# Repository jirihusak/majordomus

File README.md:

# Majordmus - Open source system for Smart Home
 
## About
 
**Majordomus** is a modular automation system built on open standards. It fills the gap between closed, expensive commercial solutions and unreliable consumer-grade components — designed to be repairable, expandable, and to last for decades.
  
## Features
 
- 🧩 **Modular hardware** — base unit + interchangeable modules ( I/O, sensors)
- 🔌 **Standardized interface** — RS-485 / ModBus HW interface, MQTT SW interface
- 🔓 **Vendor lock-in free** — open hardware, open software, your choice
- 🧠 **Node-RED inside** — visual programming for automation flows
- 🧠 **Home Assistant interface** — MQTT integration for popular platform
- 📡 **Offline-first** — works without internet, cloud is optional
## Use Cases
 
| Domain | Examples |
|---|---|
| 🏠 Smart home | lighting, heating, blinds, security, energy management |
| 🏭 Industry | machine control, data acquisition, monitoring, alarms |
| 📊 Monitoring | weather, air quality, energy meters, IoT sensors |
 
## Architecture
 
```
   ┌─────────────────────┐
   │      node-RED       │
   │   Home Assistant    │
   └──────────┬──────────┘
              │
             MQTT
              │
   ┌──────────┴──────────┐
   │ Majordomus Control  │
   │    MQTT bridge      │
   └──────────┬──────────┘
              │
       Modbus / RS-485
              │
    ┌─────────┼─────────┐
    │         │         │
   Unit A   Unit B   Unit C
  (+ modules) (+ modules) (+ modules)
```
 
## Hardware
 
### 🌡️ RoomSensor
 
All-in-one ambient monitoring unit for indoor environments.
 
- 🌡️ Temperature & humidity
- 💨 CO₂, VOC & NOx measurement
- 🚶 PIR motion detection
- ☀️ Ambient light (lux)
- 🔊 Ambient noise measurement
- 🖥️ Display with 3 buttons
- 🔔 Piezo buzzer for acoustic signaling
- 🔌 Digital I/O for door/window contacts or local buttons
- 🔗 I²C port for external sensors
- 🏠 Wall-mount

### 🔲 BoxIO
 
Compact relay & input unit for in-wall or junction-box installation.
 
- ⚡ Replaceable relay outputs (electromagnetic or SSR)
- 🔘 Digital inputs for buttons
- 📊 Hardware input counters for energy monitoring
- 🎛️ Manual control of all outputs (AUTO / MAN ON / MAN OFF)
- 🔗 I²C port for external sensors

### 🎛️ RoomIO
 
Multi-purpose I/O unit for room-level automation and control.
 
- 🔘 Digital inputs & outputs
- 📥 Analog inputs (ADC) — 0–10 V
- 📤 Analog outputs (DAC) — 0–10 V for dimming, fan speed, valves
- 📊 Hardware input counters for energy monitoring
- 🔗 I²C port for external sensors

Schematics and BOMs live in [`hardware/`](hardware/).
 
## Software
 
### **Majordomus Control**
Bridge from HW modules to MQTT interface

### **Node-RED - Custom Node-RED nodes**

## Documentation

- [Documentation web](https://jirihusak.github.io/majordomus/cs/) 

## Contributing
 
Contributions welcome — hardware, firmware, Node-RED flows, or docs.

## Contact
 
- **Web:** [majordomus.tech](https://majordomus.tech)

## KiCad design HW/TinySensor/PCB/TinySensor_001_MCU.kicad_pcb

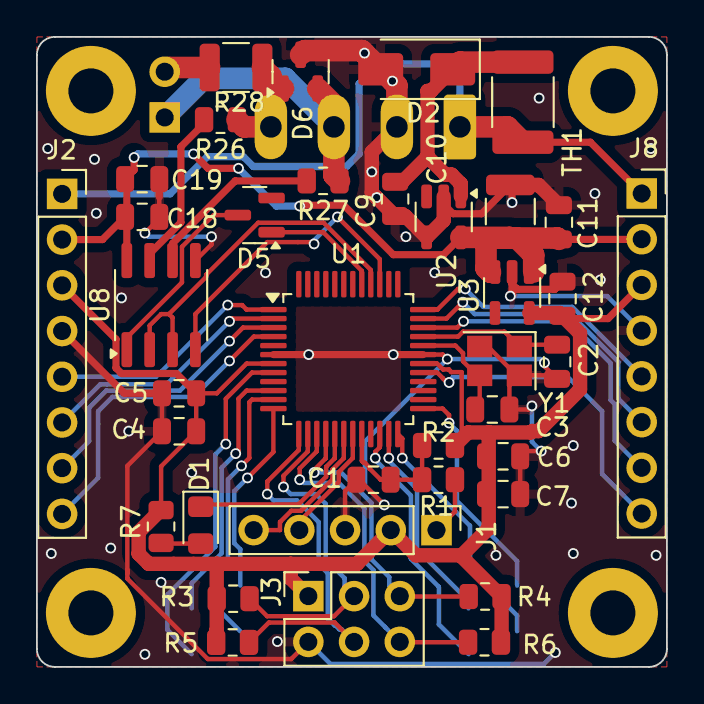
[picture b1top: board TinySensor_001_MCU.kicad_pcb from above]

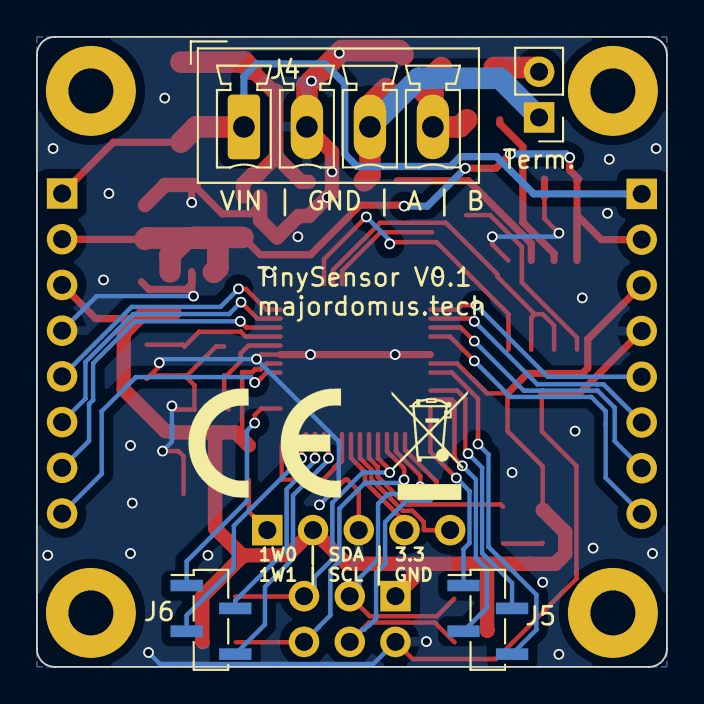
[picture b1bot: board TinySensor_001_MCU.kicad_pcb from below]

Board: 2 copper layers, 35.0 x 35.0 mm, 45 parts (4 on the bottom side), 42 nets.

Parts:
 : MountingHole_2.5mm_Pad
 #2,  #3,  #4: MountingHole_2.5mm_Pad
C1, C5, C6, C11, C18: 100nF; C_0805_2012Metric
C2, C3: 18pF; C_0805_2012Metric
C4, C7, C9, C12, C19: 1uF; C_0805_2012Metric
C10: 2.2uF; C_1210_3225Metric
D1: LED; LED_0805_2012Metric_Pad1.15x1.40mm_HandSolder
D2: SMAJ28; D_SMA
D5: BAS70LT1G; SOT-23
D6: D_TVS_x2_AAC; SOT-23
J1: CONN_DEBUG; PinHeader_1x05_P2.54mm_Vertical
J2, J8: Conn_01x08; PinSocket_1x08_P2.54mm_Vertical
J3: Conn_02x03_Odd_Even; PinSocket_2x03_P2.54mm_Vertical
J4: Conn_01x04; PhoenixContact_MCV_1,5_4-G-3.5_1x04_P3.50mm_Vertical
J5, J6: Conn_01x04; PinSocket_1x04_P1.27mm_Vertical_SMD_Pin1Left
R1: 10k; R_0805_2012Metric
R2: 100R; R_0805_2012Metric
R3, R4, R5, R6: 4k7; R_0805_2012Metric
R7: 1k; R_0805_2012Metric
R26, R27: 10R; R_0805_2012Metric
R28: 120R; R_1210_3225Metric
TH1: MF-MSMF050-2; Fuse_1812_4532Metric_Pad1.30x3.40mm_HandSolder
Term.: Jumper; PinHeader_1x02_P2.54mm_Vertical
U1: PIC18F57K42; TQFP-48_7x7mm_P0.5mm
U2: TPS709; SOT-23-5
U3: TLV70233DBVR; SOT-23-5
U8: SN65HVD3082EDR; SOIC-8_3.9x4.9mm_P1.27mm
Y1: Crystal_GND24; Crystal_SMD_SeikoEpson_FA238-4Pin_3.2x2.5mm

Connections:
+3.3V: C4.1, C5.1, C6.1, C7.1, C12.1, J1.2, J2.3, J3.1, J8.3, R1.1, R3.1, R4.1, R5.2, R6.2, R7.1, U1.7 (VDD), U1.30 (VDD), U3.5 (OUT)
+5V: C10.1, C11.1, C18.1, C19.1, J2.2, J8.2, U2.5 (OUT), U3.1 (IN), U3.3 (EN), U8.8 (VCC)
+12V: J2.1, J4.1, J8.1, TH1.2
/Connectors/RS485-A: D6.2 (A2), J4.3, R27.1, Term..1
/Connectors/RS485-B: D6.1 (A1), J4.4, R26.1, R28.2
/MCU_PIC18/A1: J6.4, U1.22 (RA1)
/MCU_PIC18/A2: J6.2, U1.23 (RA2)
/MCU_PIC18/A3: J6.3, U1.24 (RA3)
/MCU_PIC18/A4: J6.1, U1.25 (RA4)
/MCU_PIC18/B0: J5.4, U1.8 (RB0)
/MCU_PIC18/B2: J5.2, U1.10 (RB2)
/MCU_PIC18/B3: J5.3, U1.11 (RB3)
/MCU_PIC18/B4: J3.5, R4.2, U1.16 (RB4)
/MCU_PIC18/C0: J8.7, U1.34 (RC0)
/MCU_PIC18/C1: J8.6, U1.35 (RC1)
/MCU_PIC18/C7: J2.5, U1.1 (RC7)
/MCU_PIC18/D4: J2.6, U1.2 (RD4)
/MCU_PIC18/D5: J2.7, U1.3 (RD5)
/MCU_PIC18/D6: J2.8, U1.4 (RD6)
/MCU_PIC18/E2: J8.8, U1.29 (RE2)
/MCU_PIC18/F0: J8.5, U1.36 (RF0)
/MCU_PIC18/F4: J5.1, U1.12 (RF4)
/MCU_PIC18/F5: J3.4, R5.1, U1.13 (RF5)
/MCU_PIC18/F6: J3.3, R3.2, U1.14 (RF6)
/MCU_PIC18/F7: J3.6, R6.1, U1.15 (RF7)
/MCU_PIC18/RS485_RX: U1.39 (RF3), U8.4 (D)
/MCU_PIC18/RS485_TX: D5.2 (A), U1.41 (RC3)
/MCU_PIC18/RS485_TX_ENABLE: U1.40 (RC2), U8.2 (#RE), U8.3 (DE)
GND: C1.2, C2.2, C3.2, C4.2, C5.2, C6.2, C7.2, C9.2, C10.2, C11.2, C12.2, C18.2, C19.2, D2.2 (A), D6.3 (common), J1.3, J2.4, J3.2, J4.2, J8.4, U1.6 (VSS), U1.31 (VSS), U2.2 (GND), U2.4 (GND), U3.2 (GND), U8.5 (GND), Y1.2, Y1.4
ICSPCLK: J1.5, U1.18 (RB6)
ICSPDAT: J1.4, U1.19 (RB7)
LED_WORK: D1.1 (K), U1.17 (RB5)
MCLR: C1.1, R1.2, R2.1, U1.20 (MCLR/RE3)
unnamed: D1.2 (A), R7.2
unnamed: C9.1, D2.1 (K), TH1.1, U2.1 (IN)
unnamed: D5.1 (K), U8.1 (R)
unnamed: J1.1, R2.2
unnamed: R28.1, Term..2
unnamed: C2.1, U1.33 (RA6), Y1.1
unnamed: C3.1, U1.32 (RA7), Y1.3
unnamed: R27.2, U8.6 (A)
unnamed: R26.2, U8.7 (B)

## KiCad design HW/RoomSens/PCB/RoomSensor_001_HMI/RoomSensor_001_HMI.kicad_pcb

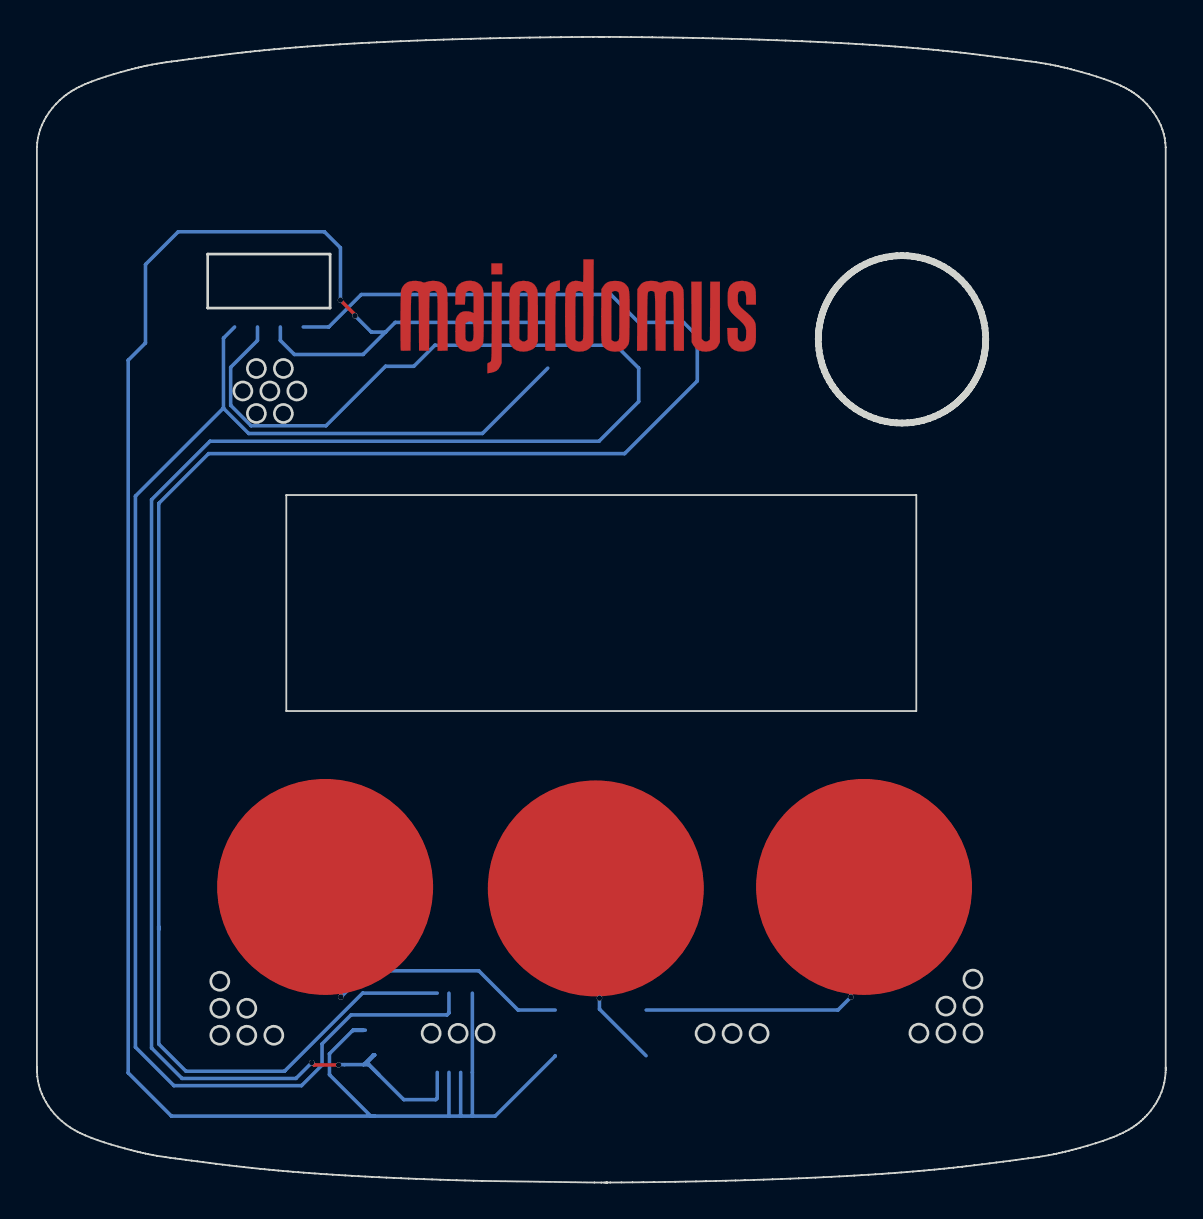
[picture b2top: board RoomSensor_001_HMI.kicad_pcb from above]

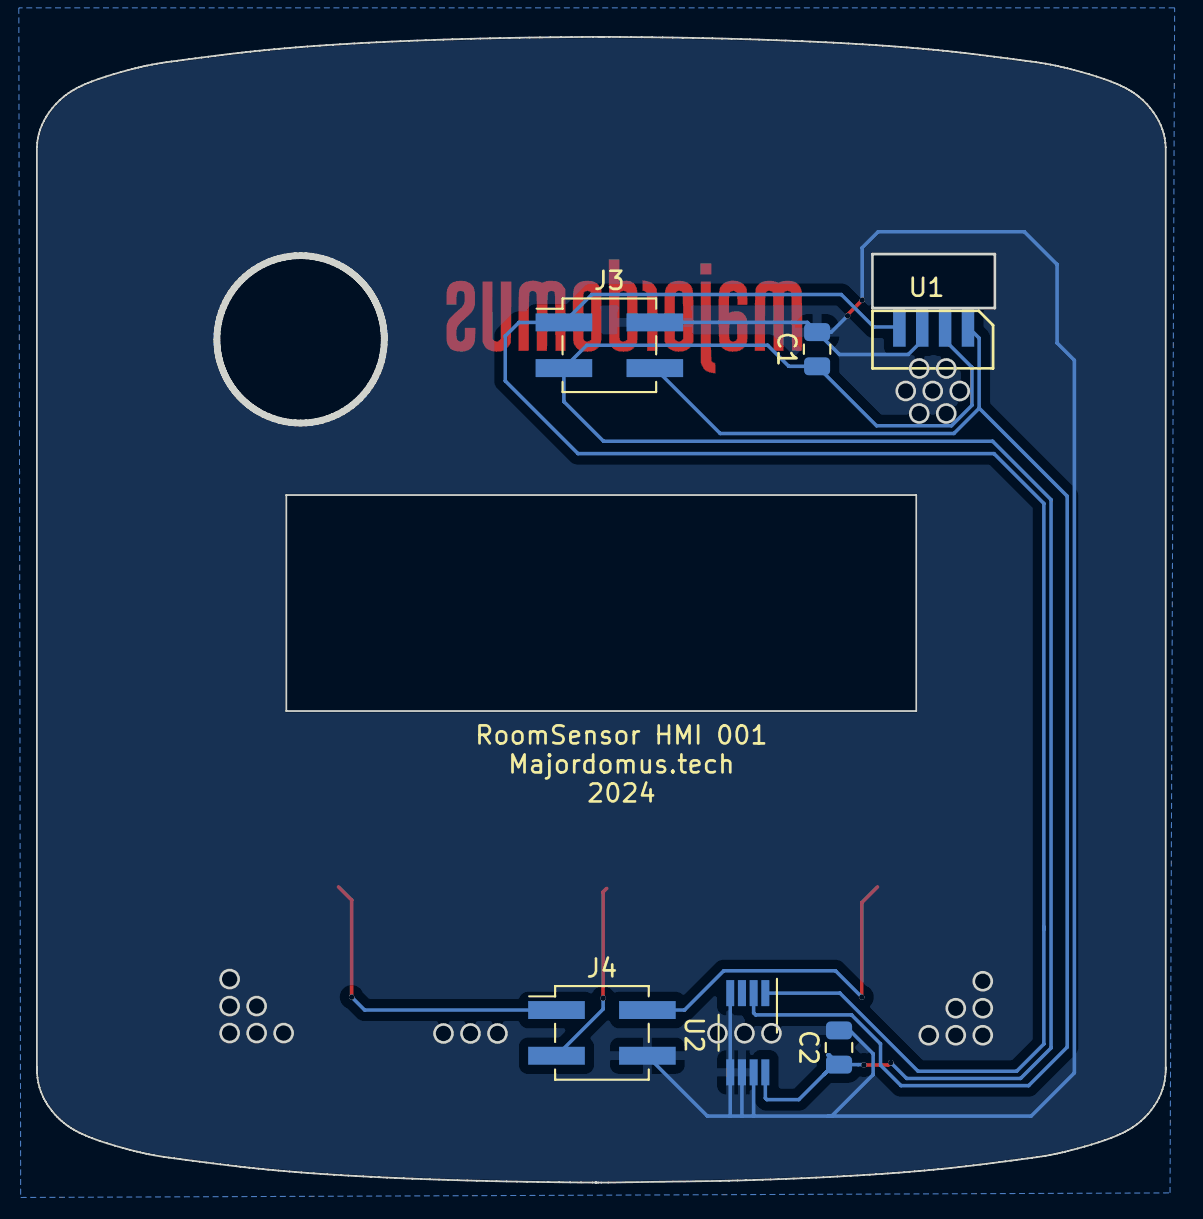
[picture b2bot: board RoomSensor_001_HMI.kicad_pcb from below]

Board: 2 copper layers, 62.4 x 63.4 mm, 9 parts (6 on the bottom side), 7 nets.

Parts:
 : Antenna; CapButtonMinus
 #2: Antenna; CapButtonEnter
 #3: Antenna; CapButtonPlus
C1, C2: C; C_0805_2012Metric
J3, J4: Conn_02x02_Odd_Even; PinHeader_2x02_P2.54mm_Vertical_SMD
U1: VEML7700-TT; VEML7700
U2: TMP1075DGK; VSSOP-8_3.0x3.0mm_P0.65mm

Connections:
+3.3V: C1.1, C2.1, J3.3, U1.2 (VDD), U2.8 (V+)
GND: C1.2, C2.2, J3.2, J4.4, U1.3 (GND), U2.4 (GND), U2.5 (A2), U2.6 (A1), U2.7 (A0)
I2C_SCL: J3.4, U1.1 (SCL), U2.2 (SCL)
I2C_SDA: J3.1, U1.4 (SDA), U2.1 (SDA)
unnamed: #3.1 (A), J4.1
unnamed: #2.1 (A), J4.3
unnamed: .1 (A), J4.2

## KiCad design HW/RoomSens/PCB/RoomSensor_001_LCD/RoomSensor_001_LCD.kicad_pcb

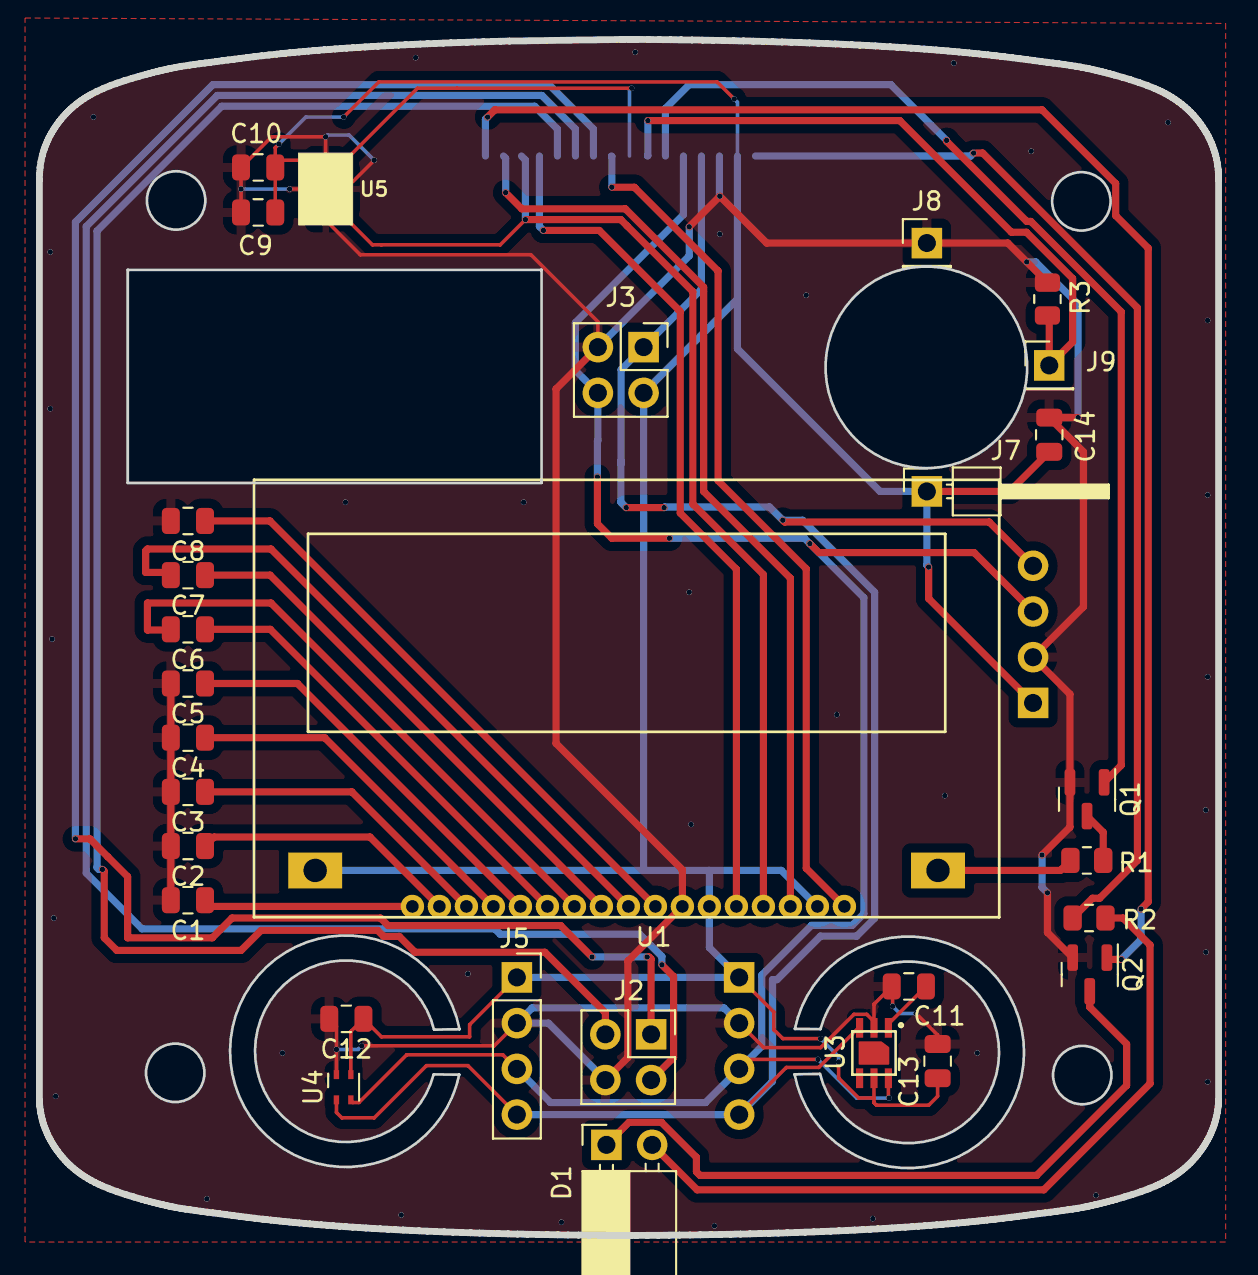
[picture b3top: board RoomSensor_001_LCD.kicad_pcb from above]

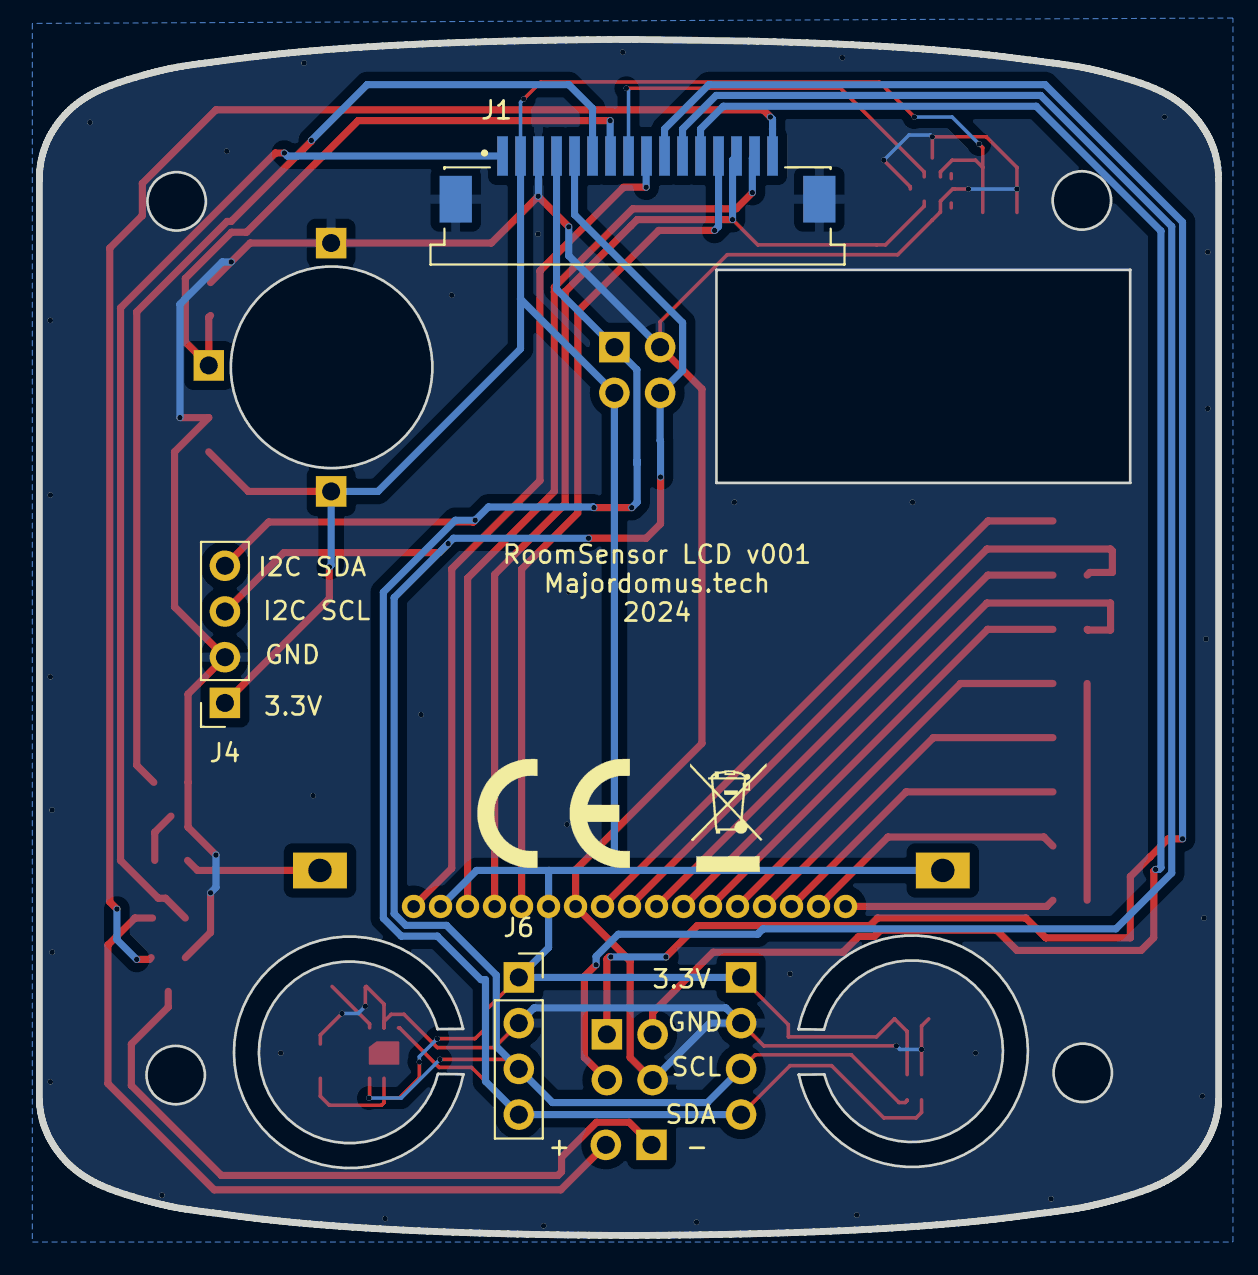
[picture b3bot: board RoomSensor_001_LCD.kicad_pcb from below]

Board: 2 copper layers, 65.5 x 66.4 mm, 33 parts (3 on the bottom side), 31 nets.

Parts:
C1, C2, C3, C4, C5: 100nF; C_0805_2012Metric
C6, C7, C8, C9, C10, C11, C12, C13, C14: 1uF; C_0805_2012Metric
D1: LED LL-234WC2Q-W5-3P; PinSocket_1x02_P2.54mm_Horizontal
J1: 68611614422; WURTH_68611614422
J2, J3: Conn_02x02_Odd_Even; PinSocket_2x02_P2.54mm_Vertical
J4, J5, J6: Conn_01x04; PinSocket_1x04_P2.54mm_Vertical
J7: Conn_01x01; PinHeader_1x01_P2.54mm_Horizontal
J8, J9: Conn_01x01; PinHeader_1x01_P2.54mm_Vertical
Q1, Q2: MMBF170; SOT-23
R1: 1k5; R_0805_2012Metric
R2: R; R_0805_2012Metric
R3: 100k; R_0805_2012Metric
U1: NHD-C12832A1Z-NSW-BBW-3V3; NHD-C12832A1Z
U3: SGP40
U4: SHT41-AD1F-R2; Sensirion_DFN-4_1.5x1.5mm_P0.8mm_SHT4x_NoCentralPad
U5: MP34DT05-A; MIC-PACK

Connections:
+3.3V: C9.1, C10.1, C12.1, C13.1, C14.1, J1.2, J3.3, J4.1, J5.1, J6.1, J7.1, U1.12 (VDD), U1.16 (/RES), U1.18 (LED_Anode_+), U3.5 (VDD), U4.3 (VDD), U5.VDD
+5V: J1.1, R2.2
/LCD_A0: J1.15, U1.15 (A0)
/LCD_BACKLIGHT: J1.6, Q1.1 (G)
/LCD_CS: J1.9, U1.17 (CS1B)
/LED_AMBIENT: J1.16, Q2.1 (G)
/PIR: J1.7, J9.1, R3.1
/SPI_MISO: J1.8, U5.DOUT
/SPI_MOSI: J1.13, U1.13 (SI)
/SPI_SCLK: J1.14, U1.14 (SCL), U5.CLK
/SW_ENTER: J1.10, J2.1
/SW_MINUS: J1.11, J2.3
/SW_PLUS: J1.12, J2.2
GND: C1.2, C2.2, C3.2, C4.2, C5.2, C8.2, C9.2, C10.2, C11.2, C12.2, C13.2, C14.2, J1.3, J1.S1 (SHIELD), J1.S2 (SHIELD), J2.4, J3.2, J4.2, J5.2, J6.2, J8.1, Q1.2 (S), Q2.2 (S), R3.2, U1.11 (VSS), U3.2 (GND), U4.4 (VSS), U5.GND, U5.GND1 (GND), U5.GND2 (GND), U5.GND3 (GND), U5.LR
I2C_SCL: J1.5, J3.4, J4.3, J5.3, J6.3, U3.6 (SCL), U4.2 (SCL)
I2C_SDA: J1.4, J3.1, J4.4, J5.4, J6.4, U3.3 (SDA), U4.1 (SDA)
unnamed: C11.1, U3.1 (VDD)
unnamed: D1.2 (A), R2.1
unnamed: D1.1 (K), Q2.3 (D)
unnamed: Q1.3 (D), R1.1
unnamed: C7.1, U1.8 (C1+)
unnamed: C7.2, U1.9 (C1-)
unnamed: C6.2, U1.7 (C2+)
unnamed: C6.1, U1.6 (C2-)
unnamed: R1.2, U1.19 (LED_Kathode_+)
unnamed: C1.1, U1.1 (V0)
unnamed: C2.1, U1.2 (V1)
unnamed: C3.1, U1.3 (V2)
unnamed: C4.1, U1.4 (V3)
unnamed: C5.1, U1.5 (V4)
unnamed: C8.1, U1.10 (VOUT)

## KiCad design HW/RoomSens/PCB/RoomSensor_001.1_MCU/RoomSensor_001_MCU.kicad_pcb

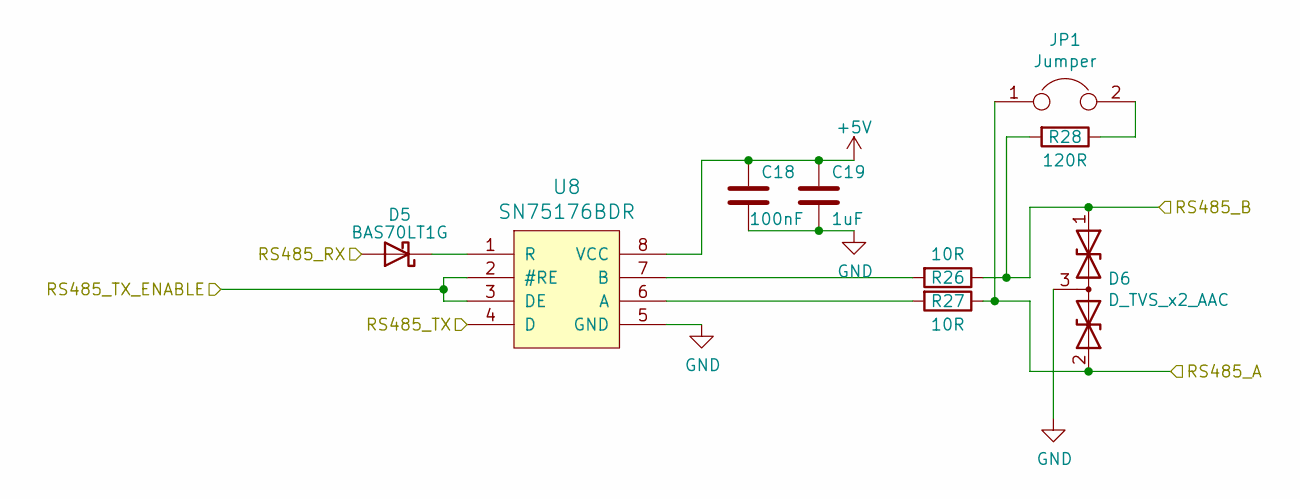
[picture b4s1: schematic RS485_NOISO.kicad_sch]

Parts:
C18: 100nF; C_0805_2012Metric
C19: 1uF; C_0805_2012Metric
D5: BAS70LT1G; SOT-23
D6: D_TVS_x2_AAC; SOT-23
JP1: Jumper; PinHeader_1x02_P2.54mm_Vertical
R26, R27: 10R; R_0805_2012Metric
R28: 120R; R_1210_3225Metric
U8: SN75176BDR; SOIC-8_3.9x4.9mm_P1.27mm

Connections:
+5V: C18.1, C19.1, U8.8 (VCC); also elsewhere on the board
/Connectors/RS485-A: D6.2 (A2), JP1.1, R27.1; also elsewhere on the board
/Connectors/RS485-B: D6.1 (A1), R26.1, R28.2; also elsewhere on the board
/MCU_PIC18/RS485_RX: U8.4 (D); also elsewhere on the board
/MCU_PIC18/RS485_TX: D5.2 (A); also elsewhere on the board
/MCU_PIC18/RS485_TX_ENABLE: U8.2 (#RE), U8.3 (DE); also elsewhere on the board
GND: C18.2, C19.2, D6.3 (common), U8.5 (GND); also elsewhere on the board
unnamed: D5.1 (K), U8.1 (R)
unnamed 63: JP1.2, R28.1; also elsewhere on the board
unnamed: R27.2, U8.6 (A)
unnamed: R26.2, U8.7 (B)

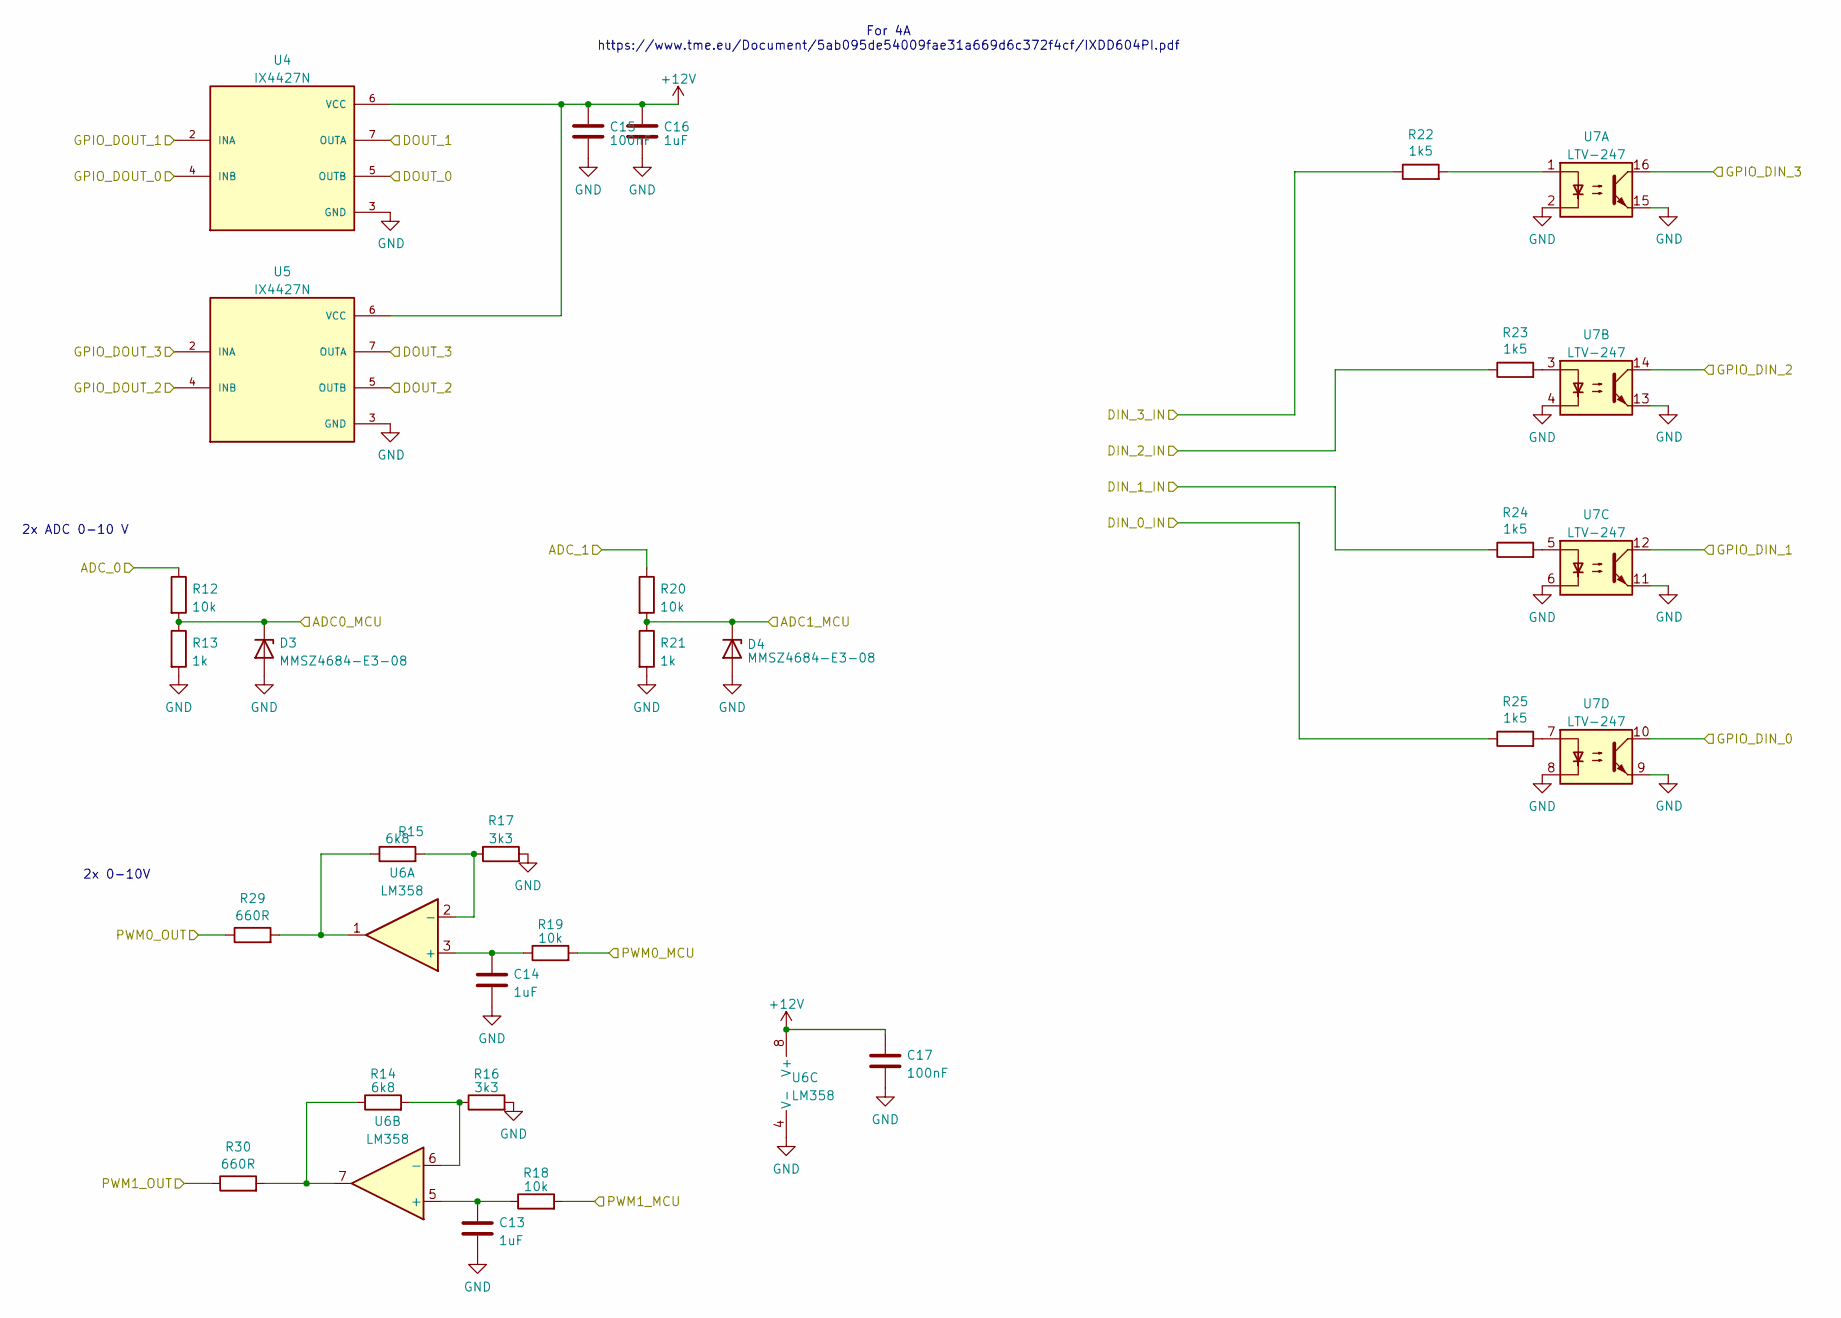
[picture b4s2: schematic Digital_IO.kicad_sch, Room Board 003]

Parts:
C13, C14, C16: 1uF; C_0805_2012Metric
C15, C17: 100nF; C_0805_2012Metric
D3, D4: MMSZ4684-E3-08; D_SOD-123
R12, R18, R19, R20: 10k; R_0805_2012Metric
R13, R21: 1k; R_0805_2012Metric
R14, R15: 6k8; R_0805_2012Metric
R16, R17: 3k3; R_0805_2012Metric
R22, R23, R24, R25: 1k5; R_0805_2012Metric
R29, R30: 660R; R_0805_2012Metric
U4, U5: IX4427N; SOIC-8_3.9x4.9mm_P1.27mm
U6: LM358; TSSOP-8_4.4x3mm_P0.65mm
U7: LTV-247; SOP-16_4.4x10.4mm_P1.27mm

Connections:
+12V: C15.1, C16.1, C17.1, U4.6 (VCC), U5.6 (VCC), U6.8 (V+); also elsewhere on the board
/Connectors/ADC_0: R12.1; also elsewhere on the board
/Connectors/ADC_1: R20.1; also elsewhere on the board
/Connectors/DAC_0: R29.1; also elsewhere on the board
/Connectors/DAC_1: R30.1; also elsewhere on the board
/Connectors/DIN_0: R25.1; also elsewhere on the board
/Connectors/DIN_1: R24.1; also elsewhere on the board
/Connectors/DIN_2: R23.1; also elsewhere on the board
/Connectors/DIN_3: R22.1; also elsewhere on the board
/Connectors/DOUT_0: U4.5 (OUTB); also elsewhere on the board
/Connectors/DOUT_1: U4.7 (OUTA); also elsewhere on the board
/Connectors/DOUT_2: U5.5 (OUTB); also elsewhere on the board
/Connectors/DOUT_3: U5.7 (OUTA); also elsewhere on the board
/Digital IO/ADC0_MCU: D3.1 (K), R12.2, R13.1; also elsewhere on the board
/Digital IO/ADC1_MCU: D4.1 (K), R20.2, R21.1; also elsewhere on the board
/Digital IO/GPIO_DIN_0: U7.10; also elsewhere on the board
/Digital IO/GPIO_DIN_1: U7.12; also elsewhere on the board
/Digital IO/GPIO_DIN_2: U7.14; also elsewhere on the board
/Digital IO/GPIO_DIN_3: U7.16; also elsewhere on the board
/Digital IO/GPIO_DOUT_0: U4.4 (INB); also elsewhere on the board
/Digital IO/GPIO_DOUT_1: U4.2 (INA); also elsewhere on the board
/Digital IO/GPIO_DOUT_2: U5.4 (INB); also elsewhere on the board
/Digital IO/GPIO_DOUT_3: U5.2 (INA); also elsewhere on the board
/Digital IO/PWM0_MCU: R19.2; also elsewhere on the board
/Digital IO/PWM1_MCU: R18.2; also elsewhere on the board
GND: C13.2, C14.2, C15.2, C16.2, C17.2, D3.2 (A), D4.2 (A), R13.2, R16.2, R17.2, R21.2, U4.3 (GND), U5.3 (GND), U6.4 (V-), U7.2, U7.4, U7.6, U7.8, U7.9, U7.11, U7.13, U7.15; also elsewhere on the board
unnamed: R14.1, R30.2, U6.7
unnamed: R15.1, R29.2, U6.1
unnamed: R22.2, U7.1
unnamed: R23.2, U7.3
unnamed: R24.2, U7.5
unnamed: R25.2, U7.7
unnamed: C14.1, R19.1, U6.3 (+)
unnamed: R15.2, R17.1, U6.2 (-)
unnamed: C13.1, R18.1, U6.5 (+)
unnamed: R14.2, R16.1, U6.6 (-)

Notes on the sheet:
2x 0-10V
2x ADC 0-10 V
For 4A https://www.tme.eu/Document/5ab095de54009fae31a669d6c372f4cf/IXDD604PI.pdf

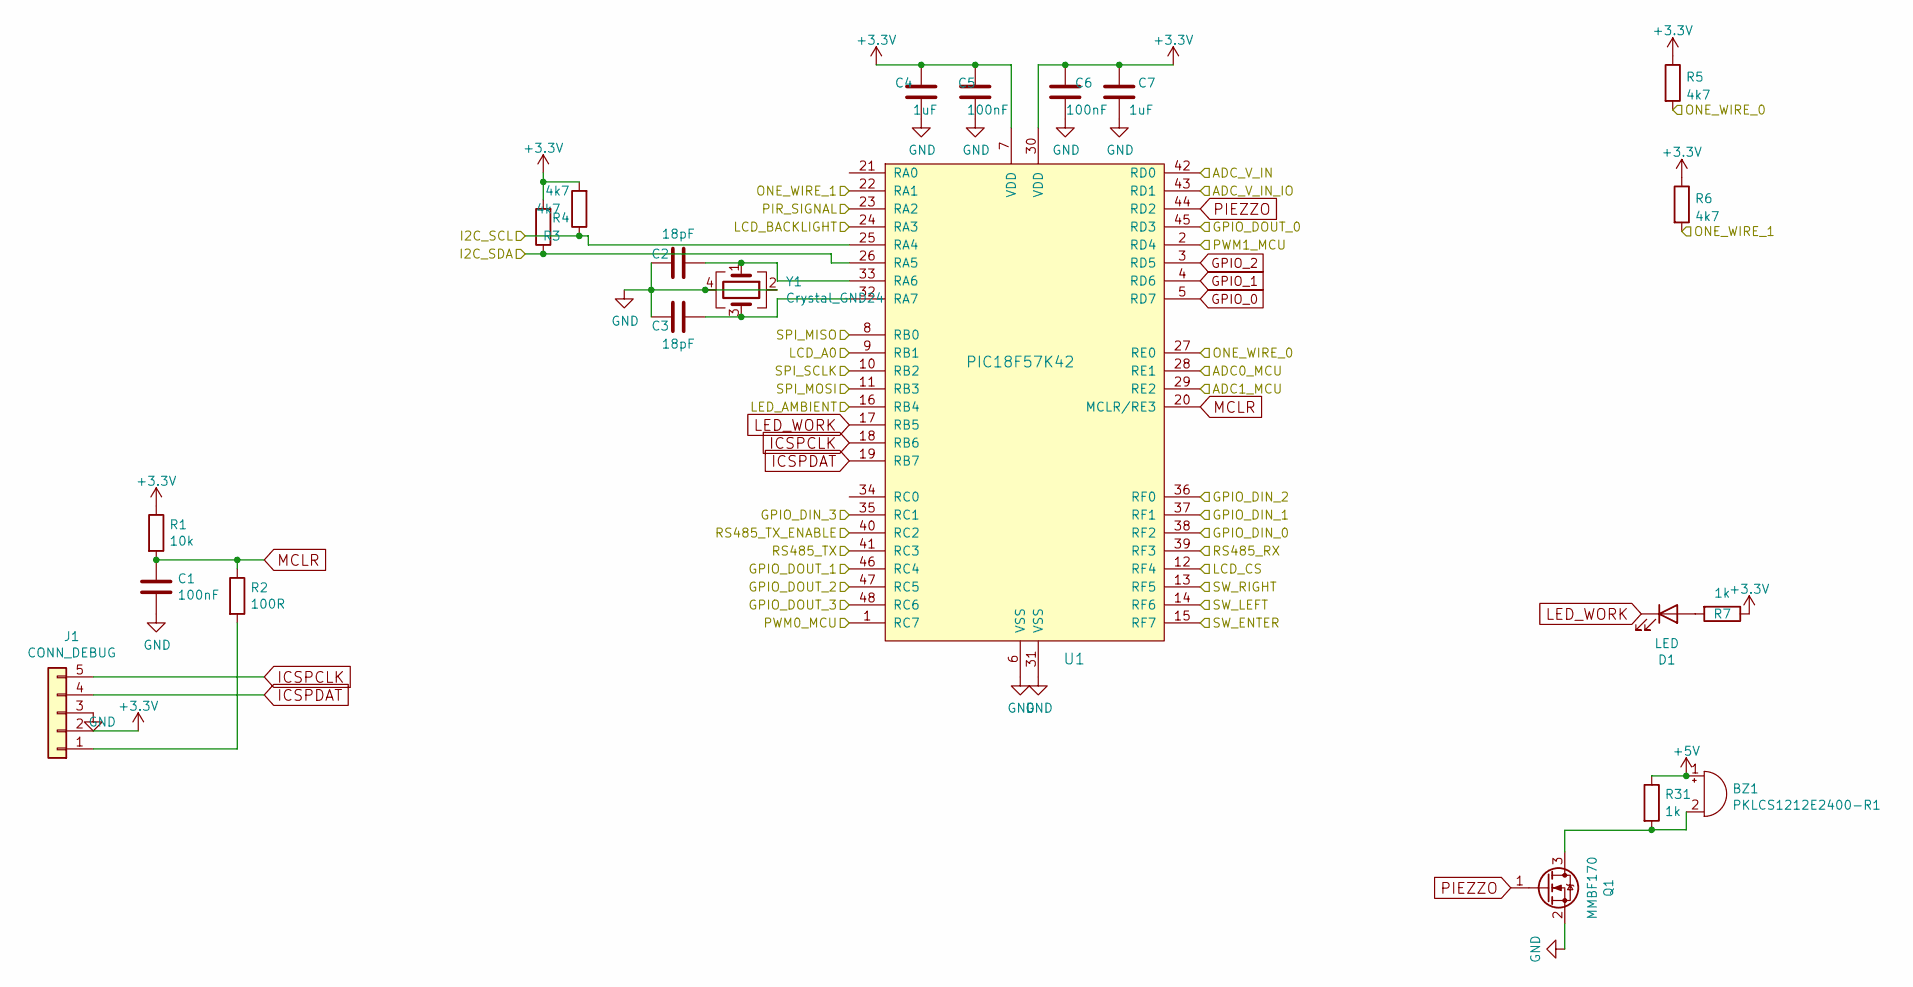
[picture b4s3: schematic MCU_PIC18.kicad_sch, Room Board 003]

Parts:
BZ1: PKLCS1212E2400-R1; Buzzer_Murata_PKLCS1212E
C1, C5, C6: 100nF; C_0805_2012Metric
C2, C3: 18pF; C_0805_2012Metric
C4, C7: 1uF; C_0805_2012Metric
D1: LED; LED_0805_2012Metric_Pad1.15x1.40mm_HandSolder
J1: CONN_DEBUG; PinHeader_1x05_P2.54mm_Vertical
Q1: MMBF170; SOT-23
R1: 10k; R_0805_2012Metric
R2: 100R; R_0805_2012Metric
R3, R4, R5, R6: 4k7; R_0805_2012Metric
R7, R31: 1k; R_0805_2012Metric
U1: PIC18F57K42; TQFP-48_7x7mm_P0.5mm
Y1: Crystal_GND24; Crystal_SMD_SeikoEpson_FA238-4Pin_3.2x2.5mm

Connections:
+3.3V: C4.1, C5.1, C6.1, C7.1, J1.2, R1.1, R3.2, R4.2, R5.1, R6.1, R7.1, U1.7 (VDD), U1.30 (VDD); also elsewhere on the board
+5V: BZ1.1 (-), R31.1; also elsewhere on the board
/Connectors/I2C_SCL: R4.1, U1.25 (RA4); also elsewhere on the board
/Connectors/I2C_SDA: R3.1, U1.26 (RA5); also elsewhere on the board
/Connectors/LCD_A0: U1.9 (RB1); also elsewhere on the board
/Connectors/LCD_BACKLIGHT: U1.24 (RA3); also elsewhere on the board
/Connectors/LCD_CS: U1.12 (RF4); also elsewhere on the board
/Connectors/LED_AMBIENT: U1.16 (RB4); also elsewhere on the board
/Connectors/ONE_WIRE_0: R5.2, U1.27 (RE0); also elsewhere on the board
/Connectors/ONE_WIRE_1: R6.2, U1.22 (RA1); also elsewhere on the board
/Connectors/PIR: U1.23 (RA2); also elsewhere on the board
/Connectors/SPI_MISO: U1.8 (RB0); also elsewhere on the board
/Connectors/SPI_MOSI: U1.11 (RB3); also elsewhere on the board
/Connectors/SPI_SCLK: U1.10 (RB2); also elsewhere on the board
/Connectors/SW_ENTER: U1.15 (RF7); also elsewhere on the board
/Connectors/SW_MINUS: U1.14 (RF6); also elsewhere on the board
/Connectors/SW_PLUS: U1.13 (RF5); also elsewhere on the board
/Digital IO/ADC0_MCU: U1.28 (RE1); also elsewhere on the board
/Digital IO/ADC1_MCU: U1.29 (RE2); also elsewhere on the board
/Digital IO/GPIO_DIN_0: U1.38 (RF2); also elsewhere on the board
/Digital IO/GPIO_DIN_1: U1.37 (RF1); also elsewhere on the board
/Digital IO/GPIO_DIN_2: U1.36 (RF0); also elsewhere on the board
/Digital IO/GPIO_DIN_3: U1.35 (RC1); also elsewhere on the board
/Digital IO/GPIO_DOUT_0: U1.45 (RD3); also elsewhere on the board
/Digital IO/GPIO_DOUT_1: U1.46 (RC4); also elsewhere on the board
/Digital IO/GPIO_DOUT_2: U1.47 (RC5); also elsewhere on the board
/Digital IO/GPIO_DOUT_3: U1.48 (RC6); also elsewhere on the board
/Digital IO/PWM0_MCU: U1.1 (RC7); also elsewhere on the board
/Digital IO/PWM1_MCU: U1.2 (RD4); also elsewhere on the board
/MCU_PIC18/ADC_V_IN: U1.42 (RD0); also elsewhere on the board
/MCU_PIC18/ADC_V_IN_IO: U1.43 (RD1); also elsewhere on the board
/MCU_PIC18/RS485_RX: U1.39 (RF3); also elsewhere on the board
/MCU_PIC18/RS485_TX: U1.41 (RC3); also elsewhere on the board
/MCU_PIC18/RS485_TX_ENABLE: U1.40 (RC2); also elsewhere on the board
GND: C1.2, C2.2, C3.2, C4.2, C5.2, C6.2, C7.2, J1.3, Q1.2 (S), U1.6 (VSS), U1.31 (VSS), Y1.2, Y1.4; also elsewhere on the board
GPIO_0: U1.5 (RD7)
GPIO_1: U1.4 (RD6)
GPIO_2: U1.3 (RD5)
ICSPCLK: J1.5, U1.18 (RB6); also elsewhere on the board
ICSPDAT: J1.4, U1.19 (RB7); also elsewhere on the board
LED_WORK: D1.1 (K), U1.17 (RB5)
MCLR: C1.1, R1.2, R2.1, U1.20 (MCLR/RE3)
unnamed: BZ1.2 (+), Q1.3 (D), R31.2
unnamed: D1.2 (A), R7.2
unnamed 62: J1.1, R2.2; also elsewhere on the board
unnamed: C2.1, U1.33 (RA6), Y1.1
unnamed: C3.1, U1.32 (RA7), Y1.3
PIEZZO: Q1.1 (G), U1.44 (RD2)

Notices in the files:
HW/RoomIO/FW/RoomIO.X/mcc_generated_files/pin_manager.h:
(c) 2018 Microchip Technology Inc. and its subsidiaries.
